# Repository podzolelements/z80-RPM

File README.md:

# The z80 Rapid Prototyping Module v1.1

---

---

The z80 RPM is a credit-card sized single board computer designed for prototyping hardware for the z80. With 8 built-in IO device select pins and every signal on the z80 available as a breakout, new hardware can quickly be tested and iterated upon, without the hassle of connecting the hardware to an existing z80 system. I wanted to create something of a 1980's Arduino: enough hardware to get a fully functional system, while keeping the footprint as small as possible and with all the signals exposed so I could hook up anything I want to it. I also designed the board around being able to add shields or hats for standalone z80 projects.

# Hardware Features

- 3 Memory Configurations (selectable via jumpers on board):
  
  - 56kb RAM and 8kb ROM (both 16k and 8k jumpers)
  
  - 48kb RAM and 16kb ROM (16k jumper)
  
  - 32kb RAM and 32kb ROM (no jumpers)

- 8 IO 'Chip Select' pins connected to bits A5-A7

- ZIF socket for easy ROM replacement

- Automatic reset on power up with manual reset button

- 90mm by 57mm footprint

- Entirety of the z80's pins are accessible and labeled via breakout

# Memory & IO Address Map

56k/8k memory configuration:

- ROM: 0x0000 - 0x1fff

- RAM: 0x2000 - 0xffff

48k/16k memory configuration:

- ROM: 0x0000 - 0x3fff

- RAM: 0x4000 - 0xffff

32k/32k memory configuration:

- ROM: 0x0000 - 0x7fff

- RAM: 0x8000 - 0xffff

IO map:

- 0b000xxxxx: IO device select 0

- 0b001xxxxx: IO device select 1

- 0b010xxxxx: IO device select 2

- 0b011xxxxx: IO device select 3

- 0b100xxxxx: IO device select 4

- 0b101xxxxx: IO device select 5

- 0b110xxxxx: IO device select 6

- 0b111xxxxx: IO device select 7

# Pinout

*Note this is the board layout from v1.0, however the pin locations have not changed*

Going clockwise starting from the top:

- Orange - Memory configuration jumpers

- Purple - Data signals

- White - Clock and reset

- Blue - Data bus

- Pink - z80 signals

- Yellow - IO device selects

- Green - Address bus

Some notes: Red and Black are +5v and GND respectively. Due to limited space on the board, the IO device select lines are not labeled. IO device 0 is at the top, device 1 is below device 0, etc, and device 7 is on the bottom, right above the lower +5v connection.

# Schematic

A PDF version is also available in the schematics folder.

# Bill of Materials

If you'd like to recreate this project, here are all the parts on the PCB. Other parts likely can be substituted in, but be sure to check with the datasheets to ensure they are actually compatible. As a side note, I socket all of my IC's, which allows the removal of the IC's from the board, but they are not absolutely necessary.

| Part Reference    | Value                  | Purpose                        |
| ----------------- | ---------------------- | ------------------------------ |
| C2,C3,C4,C5,C6,C7 | .1uF                   | Decoupling capacitors          |
| C1                | .1uF                   | Automatic reset circuit        |
| D1                | 1N40001                | Automatic reset circuit        |
| R1                | 10k                    | Automatic reset circuit        |
| R2                | 100                    | Automatic reset circuit        |
| R3,R4             | 2k                     | Memory configuration pulldowns |
| RN1               | 10k                    | z80 input pin pullups          |
| SW1               | Tactile switch         | Manual reset button            |
| U1                | 27C512 (ZIF 28 socket) | 64k EEPROM                     |
| U2                | 24M512                 | 64k SRAM                       |
| U3                | z80 CPU                | CPU                            |
| U4                | 74LS32                 | Memory configuration logic     |
| U5                | 74LS138                | IO device port decoder         |
| X1                | DIP 14 oscillator can  | CPU clock                      |

# Images

*Note all images are from v1.0*

Here's the RPM in action (I've got it hooked up to an SAA1099 here):

Build progress:

This project is open source and can be used for any purpose in compliance with the GPLv3, but comes with absolutely NO WARRANTY of any kind.

Thanks for checking out my project! If you find this project useful or interesting, I'd love to hear about it!

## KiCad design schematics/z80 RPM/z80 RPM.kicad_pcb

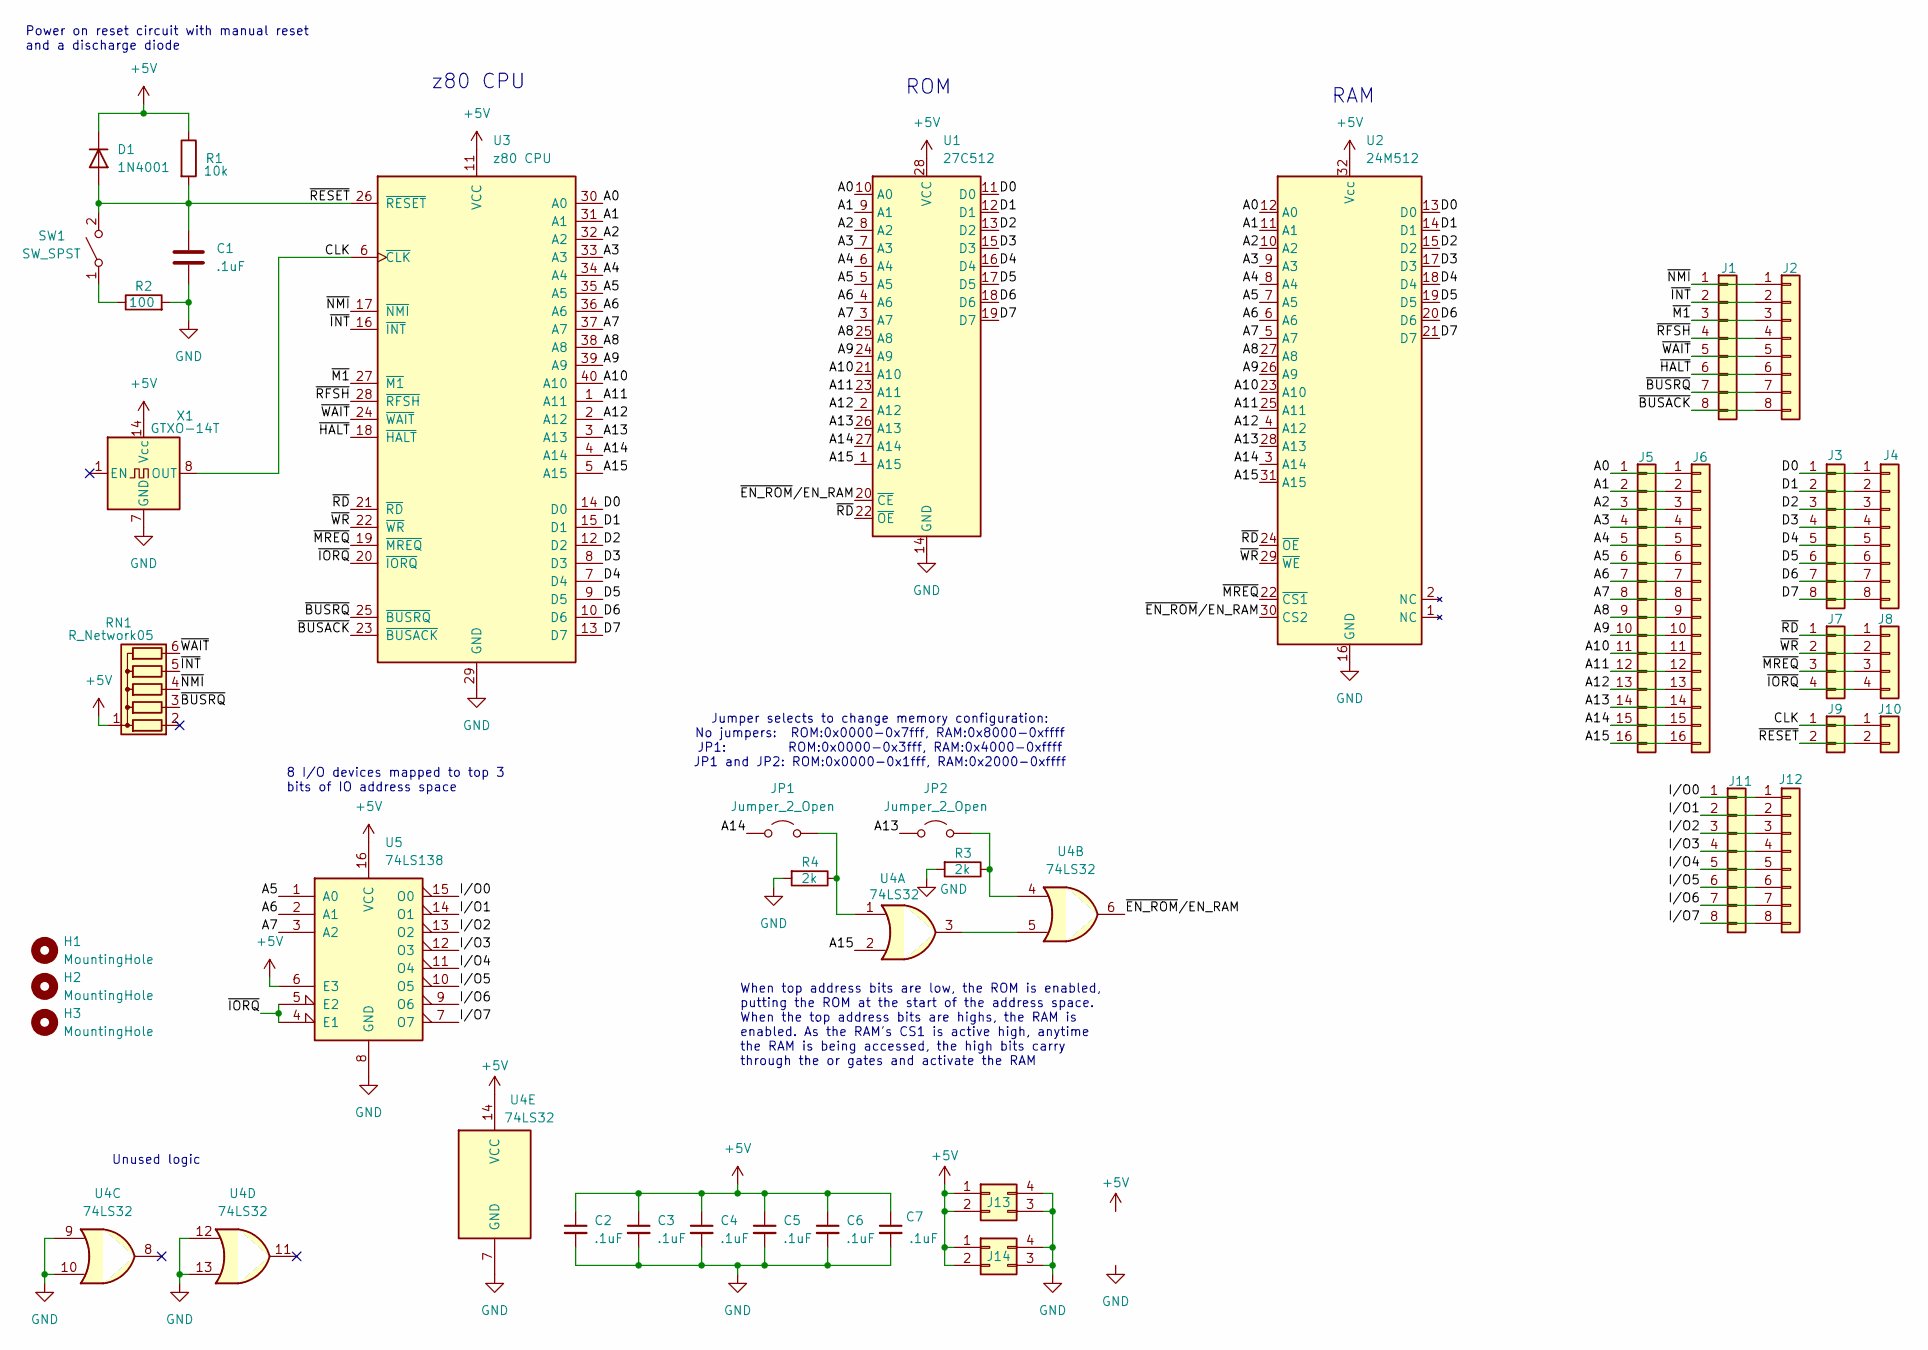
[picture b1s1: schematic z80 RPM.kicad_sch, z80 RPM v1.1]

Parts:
C1, C2, C3, C4, C5, C6, C7: .1uF; C_Disc_D3.0mm_W1.6mm_P2.50mm
D1: 1N4001; D_DO-41_SOD81_P7.62mm_Horizontal
H1, H2, H3: MountingHole; MountingHole_3.2mm_M3_DIN965_Pad_TopBottom
J1, J2, J3, J4, J11, J12: Conn_01x08; PinSocket_1x08_P2.54mm_Vertical
J5, J6: Conn_01x16; PinSocket_1x16_P2.54mm_Vertical
J7, J8: Conn_01x04; PinSocket_1x04_P2.54mm_Vertical
J9, J10: Conn_01x02; PinSocket_1x02_P2.54mm_Vertical
J13, J14: Conn_02x02_Counter_Clockwise; PinSocket_2x02_P2.54mm_Vertical
JP1, JP2: Jumper_2_Open; PinHeader_1x02_P2.54mm_Vertical
R1: 10k; R_Axial_DIN0207_L6.3mm_D2.5mm_P10.16mm_Horizontal
R2: 100; R_Axial_DIN0207_L6.3mm_D2.5mm_P10.16mm_Horizontal
R3, R4: 2k; R_Axial_DIN0207_L6.3mm_D2.5mm_P10.16mm_Horizontal
RN1: R_Network05; R_Array_SIP6
SW1: SW_SPST; SW_Tactile_SPST_Angled_PTS645Vx31-2LFS
U1: 27C512; DIP_Socket-28_W11.9_W12.7_W15.24_W17.78_W18.5_3M_228-1277-0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
U2: 24M512; DIP-32_W7.62mm
U3: z80 CPU; DIP-40_W15.24mm_Socket
U4: 74LS32; DIP-14_W7.62mm_Socket
U5: 74LS138; DIP-16_W7.62mm_Socket
X1: GTXO-14T; Oscillator_DIP-14

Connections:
+5V: C2.1, C3.1, C4.1, C5.1, C6.1, C7.1, D1.1 (K), J13.1, J13.2, J14.1, J14.2, R1.1, RN1.1 (common), U1.28 (VCC), U2.32 (Vcc), U3.11 (VCC), U4.14 (VCC), U5.6 (E3), U5.16 (VCC), X1.14 (Vcc)
/A0: J5.1, J6.1, U1.10 (A0), U2.12 (A0), U3.30 (A0)
/A1: J5.2, J6.2, U1.9 (A1), U2.11 (A1), U3.31 (A1)
/A2: J5.3, J6.3, U1.8 (A2), U2.10 (A2), U3.32 (A2)
/A3: J5.4, J6.4, U1.7 (A3), U2.9 (A3), U3.33 (A3)
/A4: J5.5, J6.5, U1.6 (A4), U2.8 (A4), U3.34 (A4)
/A5: J5.6, J6.6, U1.5 (A5), U2.7 (A5), U3.35 (A5), U5.1 (A0)
/A6: J5.7, J6.7, U1.4 (A6), U2.6 (A6), U3.36 (A6), U5.2 (A1)
/A7: J5.8, J6.8, U1.3 (A7), U2.5 (A7), U3.37 (A7), U5.3 (A2)
/A8: J5.9, J6.9, U1.25 (A8), U2.27 (A8), U3.38 (A8)
/A9: J5.10, J6.10, U1.24 (A9), U2.26 (A9), U3.39 (A9)
/A10: J5.11, J6.11, U1.21 (A10), U2.23 (A10), U3.40 (A10)
/A11: J5.12, J6.12, U1.23 (A11), U2.25 (A11), U3.1 (A11)
/A12: J5.13, J6.13, U1.2 (A12), U2.4 (A12), U3.2 (A12)
/A13: J5.14, J6.14, JP2.1 (A), U1.26 (A13), U2.28 (A13), U3.3 (A13)
/A14: J5.15, J6.15, JP1.1 (A), U1.27 (A14), U2.3 (A14), U3.4 (A14)
/A15: J5.16, J6.16, U1.1 (A15), U2.31 (A15), U3.5 (A15), U4.2
/CLK: J9.1, J10.1, U3.6 (~CLK), X1.8 (OUT)
/D0: J3.1, J4.1, U1.11 (D0), U2.13 (D0), U3.14 (D0)
/D1: J3.2, J4.2, U1.12 (D1), U2.14 (D1), U3.15 (D1)
/D2: J3.3, J4.3, U1.13 (D2), U2.15 (D2), U3.12 (D2)
/D3: J3.4, J4.4, U1.15 (D3), U2.17 (D3), U3.8 (D3)
/D4: J3.5, J4.5, U1.16 (D4), U2.18 (D4), U3.7 (D4)
/D5: J3.6, J4.6, U1.17 (D5), U2.19 (D5), U3.9 (D5)
/D6: J3.7, J4.7, U1.18 (D6), U2.20 (D6), U3.10 (D6)
/D7: J3.8, J4.8, U1.19 (D7), U2.21 (D7), U3.13 (D7)
/I/O0: J11.1, J12.1, U5.15 (O0)
/I/O1: J11.2, J12.2, U5.14 (O1)
/I/O2: J11.3, J12.3, U5.13 (O2)
/I/O3: J11.4, J12.4, U5.12 (O3)
/I/O4: J11.5, J12.5, U5.11 (O4)
/I/O5: J11.6, J12.6, U5.10 (O5)
/I/O6: J11.7, J12.7, U5.9 (O6)
/I/O7: J11.8, J12.8, U5.7 (O7)
/~BUSACK: J1.8, J2.8, U3.23 (~BUSACK)
/~BUSRQ: J1.7, J2.7, RN1.3 (R2), U3.25 (~BUSRQ)
/~EN_ROM/EN_RAM: U1.20 (~CE), U2.30 (CS2), U4.6
/~HALT: J1.6, J2.6, U3.18 (~HALT)
/~INT: J1.2, J2.2, RN1.5 (R4), U3.16 (~INT)
/~IORQ: J7.4, J8.4, U3.20 (~IORQ), U5.4 (E1), U5.5 (E2)
/~M1: J1.3, J2.3, U3.27 (~M1)
/~MREQ: J7.3, J8.3, U2.22 (~CS1), U3.19 (~MREQ)
/~NMI: J1.1, J2.1, RN1.4 (R3), U3.17 (~NMI)
/~RD: J7.1, J8.1, U1.22 (~OE), U2.24 (~OE), U3.21 (~RD)
/~RESET: C1.1, D1.2 (A), J9.2, J10.2, R1.2, SW1.2 (B), U3.26 (~RESET)
/~RFSH: J1.4, J2.4, U3.28 (~RFSH)
/~WAIT: J1.5, J2.5, RN1.6 (R5), U3.24 (~WAIT)
/~WR: J7.2, J8.2, U2.29 (~WE), U3.22 (~WR)
GND: C1.2, C2.2, C3.2, C4.2, C5.2, C6.2, C7.2, J13.3, J13.4, J14.3, J14.4, R2.2, R3.2, R4.2, U1.14 (GND), U2.16 (GND), U3.29 (GND), U4.7 (GND), U4.9, U4.10, U4.12, U4.13, U5.8 (GND), X1.7 (GND)
unnamed: JP1.2 (B), R4.1, U4.1
unnamed: JP2.2 (B), R3.1, U4.4
unnamed: R2.1, SW1.1 (A)
unnamed: U4.3, U4.5

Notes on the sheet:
8 I/O devices mapped to top 3 bits of IO address space
z80 CPU
Unused logic
Jumper selects to change memory configuration: No jumpers: ROM:0x0000-0x7fff, RAM:0x8000-0xffff JP1: ROM:0x0000-0x3fff, RAM:0x4000-0xffff JP1 and JP2: ROM:0x0000-0x1fff, RAM:0x2000-0xffff
When top address bits are low, the ROM is enabled, putting the ROM at the start of the address space. When the top address bits are highs, the RAM is enabled. As the RAM's CS1 is active high, anytime the RAM is being accessed, the high bits carry through the or gates and activate the RAM
RAM
Power on reset circuit with manual reset and a discharge diode
ROM

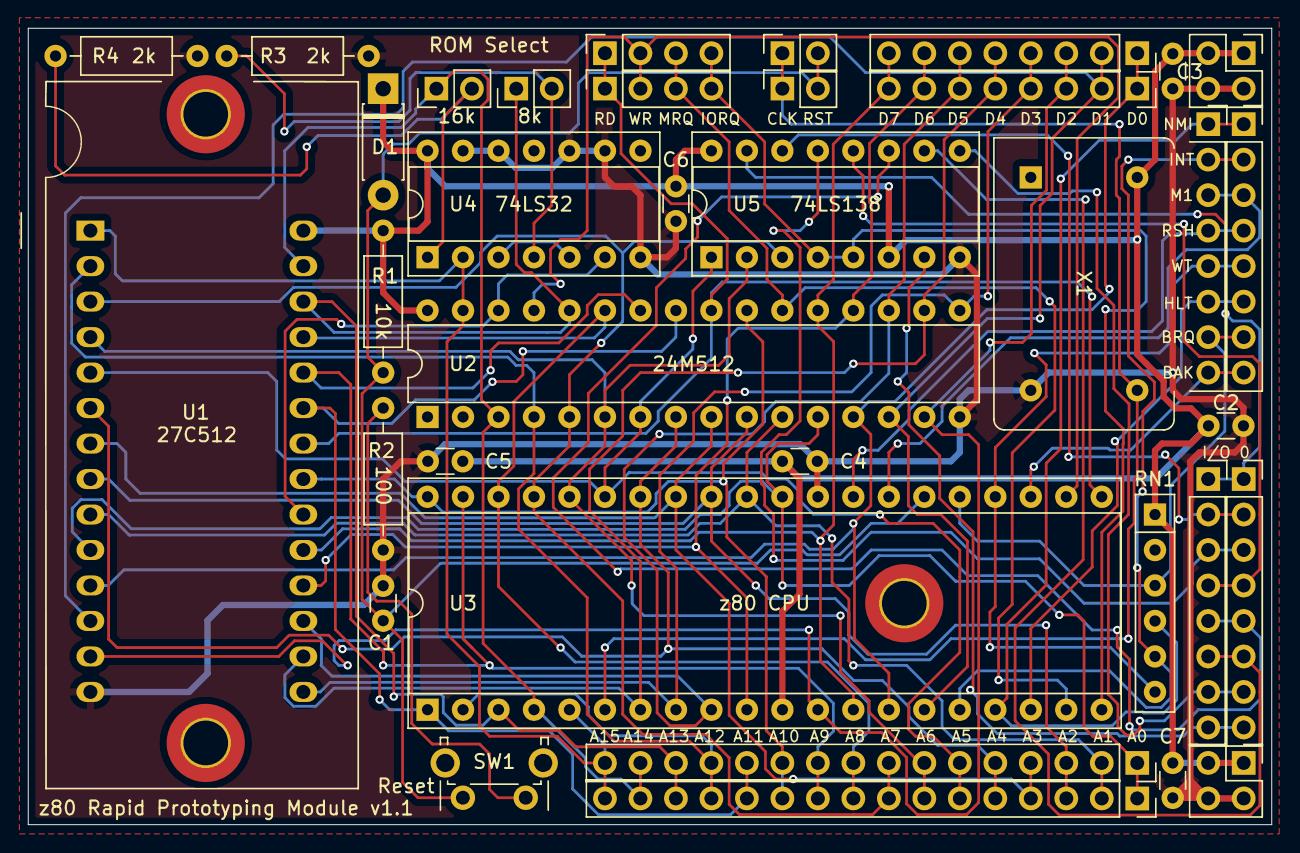
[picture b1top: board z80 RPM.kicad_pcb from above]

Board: 2 copper layers, 89.0 x 57.0 mm, 39 parts (0 on the bottom side), 53 nets.

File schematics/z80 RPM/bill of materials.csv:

"Reference","Value","Datasheet","Footprint","Qty","DNP"
"C1,C2,C3,C4,C5,C6,C7",".1uF","~","Capacitor_THT:C_Disc_D3.0mm_W1.6mm_P2.50mm","7",""
"D1","1N4001","~","Diode_THT:D_DO-41_SOD81_P7.62mm_Horizontal","1",""
"J1,J2,J3,J4,J11,J12","Conn_01x08","~","Connector_PinSocket_2.54mm:PinSocket_1x08_P2.54mm_Vertical","6",""
"J5,J6","Conn_01x16","~","Connector_PinSocket_2.54mm:PinSocket_1x16_P2.54mm_Vertical","2",""
"J7,J8","Conn_01x04","~","Connector_PinSocket_2.54mm:PinSocket_1x04_P2.54mm_Vertical","2",""
"J9,J10","Conn_01x02","~","Connector_PinSocket_2.54mm:PinSocket_1x02_P2.54mm_Vertical","2",""
"J13,J14","Conn_02x02_Counter_Clockwise","~","Connector_PinSocket_2.54mm:PinSocket_2x02_P2.54mm_Vertical","2",""
"JP1,JP2","Jumper_2_Open","~","Connector_PinHeader_2.54mm:PinHeader_1x02_P2.54mm_Vertical","2",""
"R1","10k","~","Resistor_THT:R_Axial_DIN0207_L6.3mm_D2.5mm_P10.16mm_Horizontal","1",""
"R2","100","~","Resistor_THT:R_Axial_DIN0207_L6.3mm_D2.5mm_P10.16mm_Horizontal","1",""
"R3,R4","2k","~","Resistor_THT:R_Axial_DIN0207_L6.3mm_D2.5mm_P10.16mm_Horizontal","2",""
"RN1","R_Network05","http://www.vishay.com/docs/31509/csc.pdf","Resistor_THT:R_Array_SIP6","1",""
"SW1","SW_SPST","~","Button_Switch_THT:SW_Tactile_SPST_Angled_PTS645Vx31-2LFS","1",""
"U1","27C512","http://ww1.microchip.com/downloads/en/DeviceDoc/doc0015.pdf","Socket:DIP_Socket-28_W11.9_W12.7_W15.24_W17.78_W18.5_3M_228-1277-00-0602J","1",""
"U2","24M512","","Package_DIP:DIP-32_W7.62mm","1",""
"U3","z80 CPU","www.zilog.com/manage_directlink.php?filepath=docs/z80/um0080","Package_DIP:DIP-40_W15.24mm_Socket","1",""
"U4","74LS32","http://www.ti.com/lit/gpn/sn74LS32","Package_DIP:DIP-14_W7.62mm_Socket","1",""
"U5","74LS138","http://www.ti.com/lit/gpn/sn74LS138","Package_DIP:DIP-16_W7.62mm_Socket","1",""
"X1","GTXO-14T","http://www.golledge.com/pdf/products/tcxos/gtxo14.pdf","Oscillator:Oscillator_DIP-14","1",""

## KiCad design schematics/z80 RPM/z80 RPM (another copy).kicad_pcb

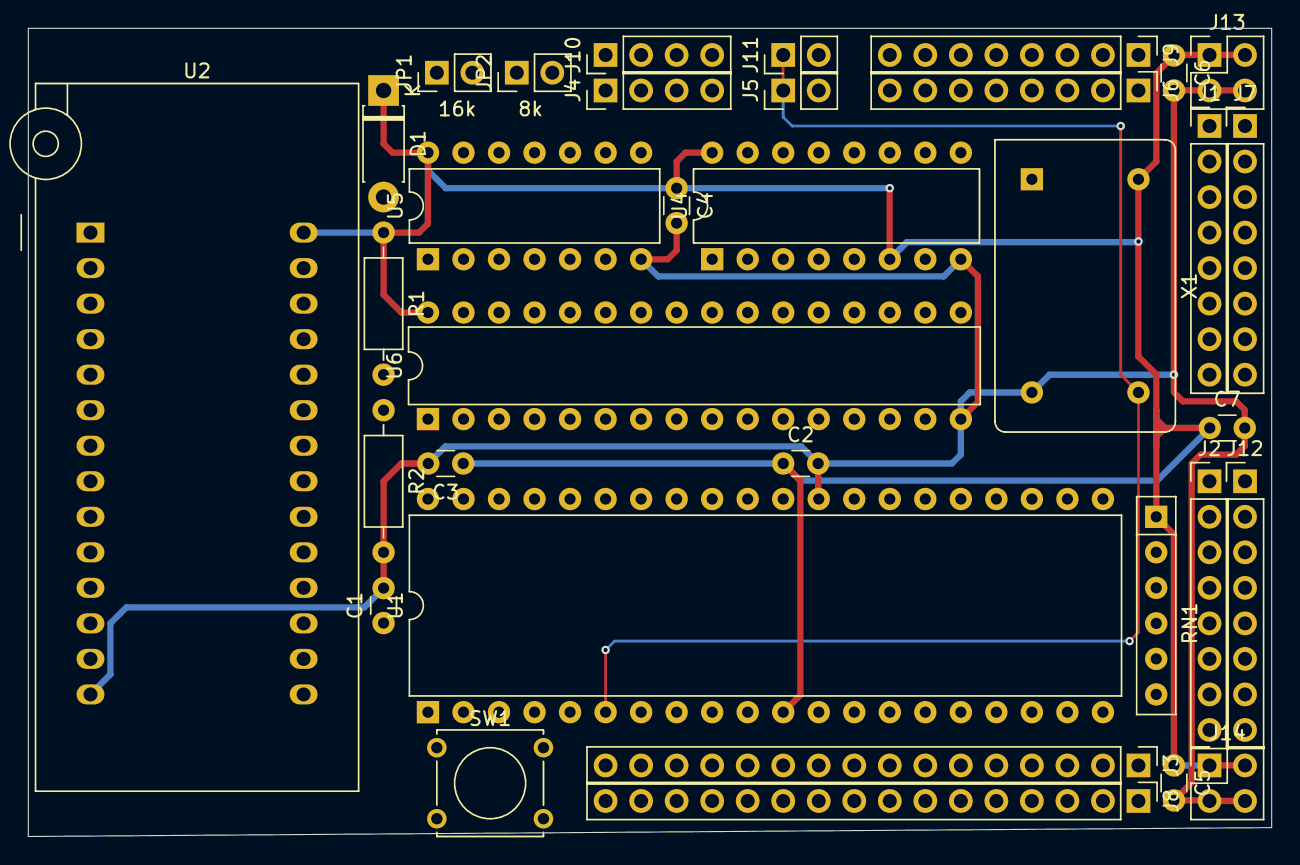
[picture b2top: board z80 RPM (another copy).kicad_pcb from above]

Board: 2 copper layers, 88.9 x 57.8 mm, 34 parts (0 on the bottom side), 53 nets.

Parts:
C1: 1uF; C_Disc_D3.0mm_W1.6mm_P2.50mm
C2, C3, C4, C5, C6, C7: C_Small; C_Disc_D3.0mm_W1.6mm_P2.50mm
D1: D; D_DO-41_SOD81_P7.62mm_Horizontal
J1, J2, J6, J7, J9, J12: Conn_01x08; PinHeader_1x08_P2.54mm_Vertical
J3, J8: Conn_01x16; PinHeader_1x16_P2.54mm_Vertical
J4, J10: Conn_01x04; PinHeader_1x04_P2.54mm_Vertical
J5, J11: Conn_01x02; PinHeader_1x02_P2.54mm_Vertical
J13, J14: Conn_02x02_Counter_Clockwise; PinHeader_2x02_P2.54mm_Vertical
JP1, JP2: Jumper_2_Open; PinHeader_1x02_P2.54mm_Vertical
R1: 1k; R_Axial_DIN0207_L6.3mm_D2.5mm_P10.16mm_Horizontal
R2: 100; R_Axial_DIN0207_L6.3mm_D2.5mm_P10.16mm_Horizontal
RN1: R_Network05; R_Array_SIP6
SW1: SW_SPST; SW_Tactile_Straight_KSA0Axx1LFTR
U1: Z80CPU; DIP-40_W15.24mm
U2: 27C512; DIP_Socket-28_W11.9_W12.7_W15.24_W17.78_W18.5_3M_228-1277-0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
U4: 74LS138; DIP-16_W7.62mm
U5: 74LS32; DIP-14_W7.62mm
U6: 24M512; DIP-32_W7.62mm
X1: GTXO-14T; Oscillator_DIP-14

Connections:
+5V: C2.1, C3.1, C4.1, C5.1, C6.1, C7.1, D1.1 (K), J13.1, J13.2, J14.1, J14.2, R1.1, RN1.1 (common), U1.11 (VCC), U2.28 (VCC), U4.6 (E3), U4.16 (VCC), U5.14 (VCC), U6.32 (Vcc), X1.14 (Vcc)
/A0: J3.1, J8.1, U1.30 (A0), U2.10 (A0), U6.12 (A0)
/A1: J3.2, J8.2, U1.31 (A1), U2.9 (A1), U6.11 (A1)
/A2: J3.3, J8.3, U1.32 (A2), U2.8 (A2), U6.10 (A2)
/A3: J3.4, J8.4, U1.33 (A3), U2.7 (A3), U6.9 (A3)
/A4: J3.5, J8.5, U1.34 (A4), U2.6 (A4), U6.8 (A4)
/A5: J3.6, J8.6, U1.35 (A5), U2.5 (A5), U4.1 (A0), U6.7 (A5)
/A6: J3.7, J8.7, U1.36 (A6), U2.4 (A6), U4.2 (A1), U6.6 (A6)
/A7: J3.8, J8.8, U1.37 (A7), U2.3 (A7), U4.3 (A2), U6.5 (A7)
/A8: J3.9, J8.9, U1.38 (A8), U2.25 (A8), U6.27 (A8)
/A9: J3.10, J8.10, U1.39 (A9), U2.24 (A9), U6.26 (A9)
/A10: J3.11, J8.11, U1.40 (A10), U2.21 (A10), U6.23 (A10)
/A11: J3.12, J8.12, U1.1 (A11), U2.23 (A11), U6.25 (A11)
/A12: J3.13, J8.13, U1.2 (A12), U2.2 (A12), U6.4 (A12)
/A13: J3.14, J8.14, JP2.1 (A), U1.3 (A13), U2.26 (A13), U6.28 (A13)
/A14: J3.15, J8.15, JP1.1 (A), U1.4 (A14), U2.27 (A14), U6.3 (A14)
/A15: J3.16, J8.16, U1.5 (A15), U2.1 (A15), U5.2, U6.31 (A15)
/CLK: J5.1, J11.1, U1.6 (~CLK), X1.8 (OUT)
/D0: J6.1, J9.1, U1.14 (D0), U2.11 (D0), U6.13 (D0)
/D1: J6.2, J9.2, U1.15 (D1), U2.12 (D1), U6.14 (D1)
/D2: J6.3, J9.3, U1.12 (D2), U2.13 (D2), U6.15 (D2)
/D3: J6.4, J9.4, U1.8 (D3), U2.15 (D3), U6.17 (D3)
/D4: J6.5, J9.5, U1.7 (D4), U2.16 (D4), U6.18 (D4)
/D5: J6.6, J9.6, U1.9 (D5), U2.17 (D5), U6.19 (D5)
/D6: J6.7, J9.7, U1.10 (D6), U2.18 (D6), U6.20 (D6)
/D7: J6.8, J9.8, U1.13 (D7), U2.19 (D7), U6.21 (D7)
/I/O0: J2.1, J12.1, U4.15 (O0)
/I/O1: J2.2, J12.2, U4.14 (O1)
/I/O2: J2.3, J12.3, U4.13 (O2)
/I/O3: J2.4, J12.4, U4.12 (O3)
/I/O4: J2.5, J12.5, U4.11 (O4)
/I/O5: J2.6, J12.6, U4.10 (O5)
/I/O6: J2.7, J12.7, U4.9 (O6)
/I/O7: J2.8, J12.8, U4.7 (O7)
/~BUSACK: J1.8, J7.8, U1.23 (~BUSACK)
/~BUSRQ: J1.7, J7.7, RN1.3 (R2), U1.25 (~BUSRQ)
/~EN_ROM/EN_RAM: U2.20 (~CE), U5.6, U6.30 (CS2)
/~HALT: J1.6, J7.6, U1.18 (~HALT)
/~INT: J1.2, J7.2, RN1.5 (R4), U1.16 (~INT)
/~IORQ: J4.4, J10.4, U1.20 (~IORQ), U4.4 (E1), U4.5 (E2)
/~M1: J1.3, J7.3, U1.27 (~M1)
/~MREQ: J4.3, J10.3, U1.19 (~MREQ), U6.22 (~CS1)
/~NMI: J1.1, J7.1, RN1.4 (R3), U1.17 (~NMI)
/~RD: J4.1, J10.1, U1.21 (~RD), U2.22 (~OE), U6.24 (~OE)
/~RESET: C1.1, D1.2 (A), J5.2, J11.2, R1.2, SW1.2 (B), U1.26 (~RESET)
/~RFSH: J1.4, J7.4, U1.28 (~RFSH)
/~WAIT: J1.5, J7.5, RN1.6 (R5), U1.24 (~WAIT)
/~WR: J4.2, J10.2, U1.22 (~WR), U6.29 (~WE)
GND: C1.2, C2.2, C3.2, C4.2, C5.2, C6.2, C7.2, J13.3, J13.4, J14.3, J14.4, R2.2, U1.29 (GND), U2.14 (GND), U4.8 (GND), U5.7 (GND), U5.9, U5.10, U5.12, U5.13, U6.16 (GND), X1.7 (GND)
unnamed: JP1.2 (B), U5.1
unnamed: JP2.2 (B), U5.4
unnamed: R2.1, SW1.1 (A)
unnamed: U5.3, U5.5

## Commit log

2024-09-25 added files
2024-09-25 added schematic images and cleaned up schematic
2024-09-26 added README
2024-10-01 design updated to v1.1
